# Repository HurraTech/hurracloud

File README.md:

### Dev Environment Setup 

1. Checkout code

        git clone --recurse-submodules https://github.com/hurratech/hurracloud.git
        git submodule foreach --recursive git checkout master
        git submodule foreach --recursive git pull origin master

2. Install dependencies

        # macOS
        brew install go leveldb tmux protoc-gen-go protoc-gen-go-grpc

        # Linux (Fedora)
        dnf install go leveldb leveldb-devel tmux protoc-gen-go

3. Install Air tool (allows hot reload of Golang app)

        curl -sSfL https://raw.githubusercontent.com/cosmtrek/air/master/install.sh | sh -s -- -b /usr/local/bin

3. Install node-modules (only needed first time or when pacakge.json has changed)

        cd src/samaa
        docker run -it -v $(pwd):/app node:14.8.0 bash
        cd /app && npm install
        exit
        cd ../..

4. This will split the terminal windows for you and start all applications (you need to tmux for this, availabla via standard package managers) 

        ./start-all.sh

5. Access the UI at [http://localhost:8080/](http://localhost:8080)

### Option B: Start Components Individually

All Go components can be started manually using Go commands as shown below, or using Air tool, in each go submodule there is a config file `.air.toml` which can be used to run the app as follows:

        air -c .air.toml

The command above should work for all Go submodules. For non-Go submodules (such as Samaa), please see the following subsections.

#### 1. Samaa (UI)

1. Install node-modules

        cd src/samaa
        docker run -it -v $(pwd):/app node:14.8.0 bash
        npm install
        exit

2. Run Docker container

        docker compose up

#### 2. Jawhar (core)
1. Create data directory (one-time)

        cd src/jawhar
        mkdir data # first time

2. Start Application - two options:  

- Using Local Souq service (have to start Souq service - see below)

        go run cmd/jawhar/jawhar.go -S http://127.0.0.1:5060
        # Or simply use air (tool that auto-build and reload whenever Go source code change):
        air -c .air.toml

- Or using Production Souq (https://souq.hurracloud.io - currently down ):

        go run cmd/jawhar/jawhar.go 

#### 3. HAgent (agent)

1. Run application

        cd src/hagent
        sudo go run server.go # sudo is needed for Disk and other privileged operations to work

        # Or simply use air (tool that auto-build and reload whenever Go source code change):
        sudo air -c .air.toml

#### 4. Zahif (files indexer)
*Optional:* Needed for search and indexing functionalities

        cd src/zahif
        go run cmd/zahif/zahif.go

        # Or simply use air (tool that auto-build and reload whenever Go source code change):
        sudo air -c .air.toml

#### 5. Souq (App Store and Update service)
*Optional:* Needed for App Store functionality

        cd src/souq
        go run cmd/souq/souq.go

        # Or simply use air (tool that auto-build and reload whenever Go source code change):
        sudo air -c .air.toml

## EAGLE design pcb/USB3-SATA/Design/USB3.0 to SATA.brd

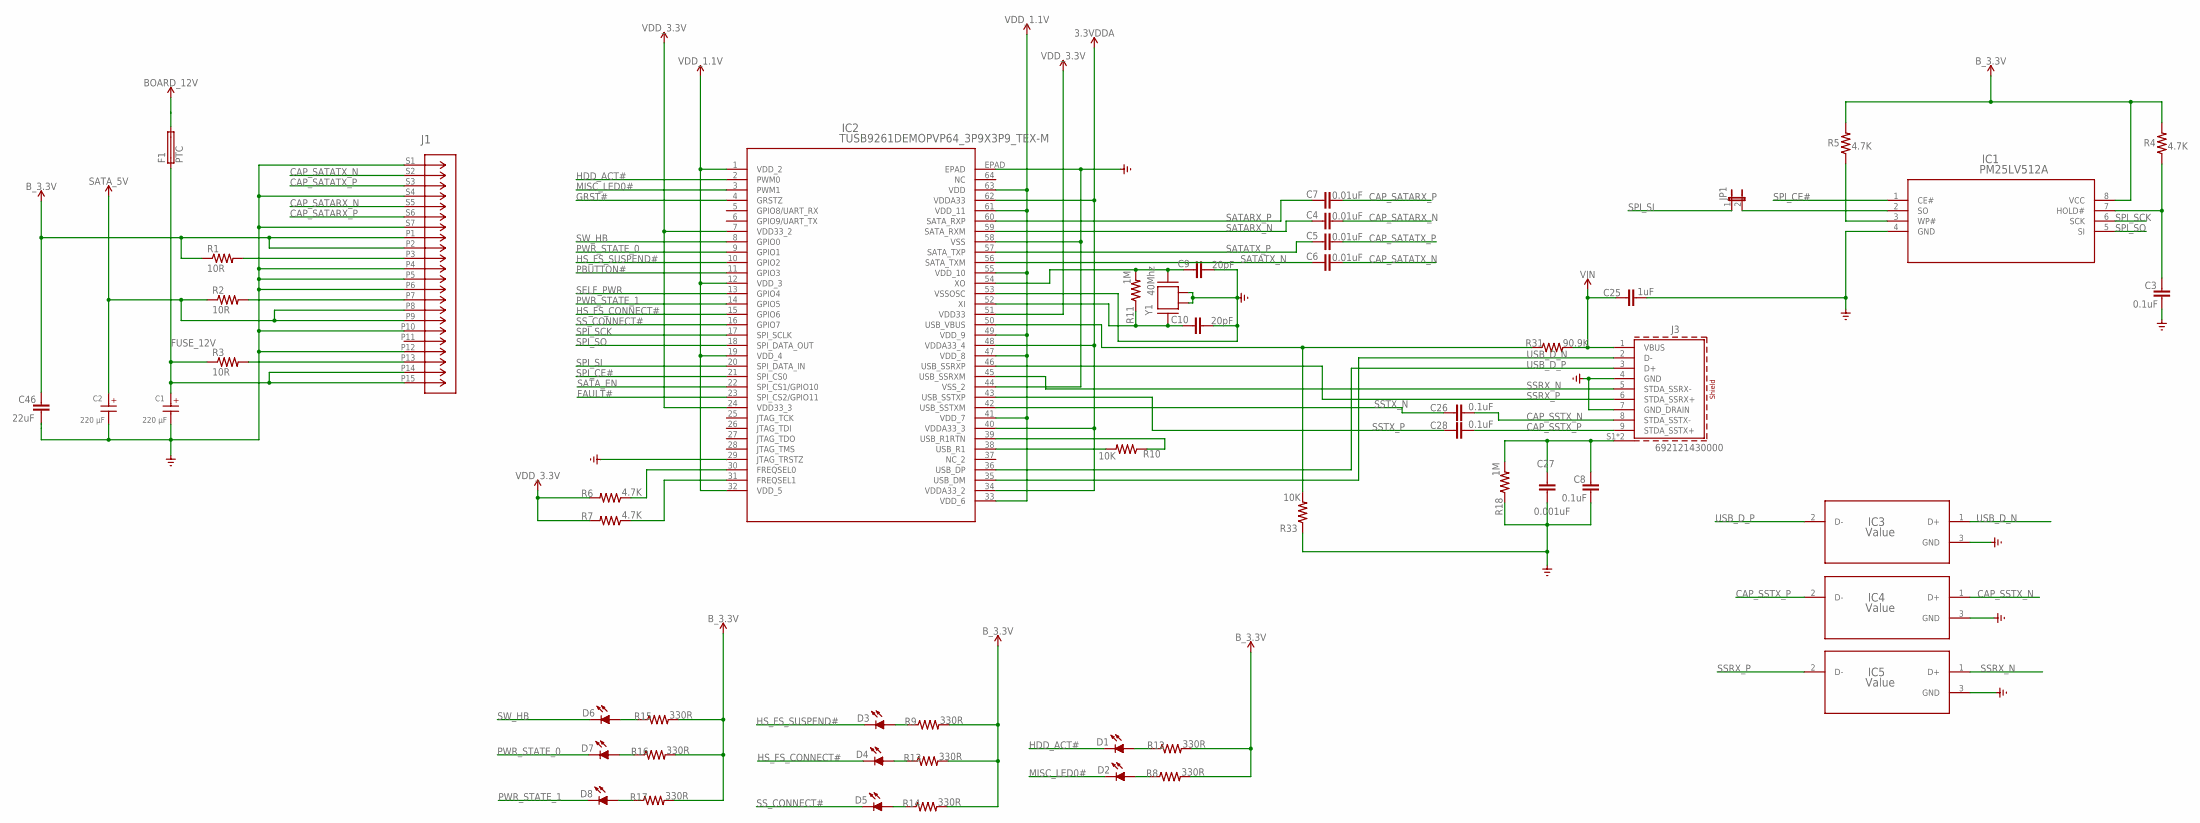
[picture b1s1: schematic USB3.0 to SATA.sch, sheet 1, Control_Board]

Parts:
C1, C2: 220 µF; WCAP-ATUL_8X11.5(DXL); MPN 860040374004
C3, C8, C26, C28: 0.1uF; CAP_0402; MPN CC0402KPX7R7BB104; DIGIKEY_PART_NUMBER 311-3559-1-ND
C4, C5, C6, C7: 0.01uF; CAP_0402; MPN GRM155R71C103KA01J; DIGIKEY_PART_NUMBER 490-6326-1-ND
C9, C10: 20pF; CAP_0402; MPN 04023U200JAT2A; DIGIKEY_PART_NUMBER 478-11758-1-ND
C25: 1uF; CAP_0402; MPN CC0402KRX5R7BB105; DIGIKEY_PART_NUMBER 311-1691-1-ND
C27: 0.001uF; CAP_0402; MPN CC0402KRX7R8BB102; DIGIKEY_PART_NUMBER 311-1712-1-ND
C46: 22uF; CAP_0402; MPN CL05A226MQ5N6J8; DIGIKEY_PART_NUMBER 1276-7090-1-ND
D1, D2, D3, D4, D5, D6, D7, D8: LED_LEDCHIP-LED0603MP; LED_CHIP-LED0603MP; DIGIKEY_PART_NUMBER 2460-L196L-SGC-TR-ND
F1: PTC; FUSC3215X82N; MPN 400CC1206LR-C-2
IC1: PM25LV512A; SOIC8-N_MC_MCH
IC2: TUSB9261DEMOPVP64_3P9X3P9_TEX-M; PVP64_3P9X3P9_TEX-M
IC3, IC4, IC5: Value; DRT0003A
J1: 10031569-001LF; CONN_10031569-001LF_AMP
J3: 692121430000
JP1: JP1E; JP1
R1, R2, R3: 10R; RES_0603; MPN SDR03EZPF10R0; DIGIKEY_PART_NUMBER 511-1693-1-ND
R4, R5, R6, R7: 4.7K; RES_0402; MPN RT0402BRD074K7L; DIGIKEY_PART_NUMBER YAG1446CT-ND
R8, R9, R12, R13, R14, R15, R16, R17: 330R; RES_0603; MPN SDR03EZPJ331; DIGIKEY_PART_NUMBER 511-1764-1-ND
R10, R33: 10K; RES_0402; MPN RCG04021M00FKED; DIGIKEY_PART_NUMBER 541-1752-1-ND
R11, R18: 1M; RES_0402; MPN RE0402BRE071ML; DIGIKEY_PART_NUMBER 13-RE0402BRE071MLCT-ND
R31: 90.9K; RES_0402; MPN RT0402DRE0790K9L; DIGIKEY_PART_NUMBER 311-2334-1-ND
Y1: 40Mhz; ABM3B-40.000MHZ-B2-T

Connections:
2.8V: IC2.7 (VDD33_2), IC2.24 (VDD33_3), IC2.51 (VDD33), R6.2, R7.2; also elsewhere on the board
3.3VDDA: IC2.34 (VDDA33_2), IC2.40 (VDDA33_3), IC2.48 (VDDA33_4), IC2.62 (VDDA33); also elsewhere on the board
5V: C2.1 (+), J1.P8, J1.P9, R2.1; also elsewhere on the board
12V: F1.2; also elsewhere on the board
B_3.3V: C46.2, IC1.8 (VCC), J1.P1, J1.P2, R1.1, R4.2, R5.2, R8.2, R9.2, R12.2, R13.2, R14.2, R15.2, R16.2, R17.2; also elsewhere on the board
CAP_SATARX_N: C4.2, J1.S5
CAP_SATARX_P: C7.2, J1.S6
CAP_SATATX_N: C6.2, J1.S2
CAP_SATATX_P: C5.2, J1.S3
CAP_SSTX_N: C26.1, IC4.1 (D+), J3.8 (STDA_SSTX-)
CAP_SSTX_P: C28.1, IC4.2 (D-), J3.9 (STDA_SSTX+)
FAULT#: IC2.23 (SPI_CS2/GPIO11); also elsewhere on the board
FUSE_12V: C1.1 (+), F1.1, J1.P14, J1.P15, R3.1
GND: C1.2 (-), C2.2 (-), C3.1, C8.1, C9.2, C10.2, C25.1, C27.2, C46.1, IC1.4 (GND), IC2.29 (JTAG_TRSTZ), IC2.44 (VSS_2), IC2.53 (VSSOSC), IC2.58 (VSS), IC2.EPAD, IC3.3 (GND), IC4.3 (GND), IC5.3 (GND), J1.P4, J1.P5, J1.P6, J1.P10, J1.P12, J1.S1, J1.S4, J1.S7, J3.4 (GND), J3.7 (GND_DRAIN), R18.1, R33.1, Y1.2, Y1.4; also elsewhere on the board
GRST#: IC2.4 (GRSTZ); also elsewhere on the board
HDD_ACT#: D1.C, IC2.2 (PWM0)
HS_FS_CONNECT#: D4.C, IC2.15 (GPIO6)
HS_FS_SUSPEND#: D3.C, IC2.10 (GPIO2)
MISC_LED0#: D2.C, IC2.3 (PWM1)
unnamed: J1.P3, R1.2
unnamed: J1.P13, R3.2
unnamed: J1.P7, R2.2
unnamed: IC1.2 (SO), JP1.2
unnamed: IC1.3 (WP#), R5.1
unnamed: C3.2, IC1.7 (HOLD#), R4.1
unnamed: IC2.30 (FREQSEL0), R6.1
unnamed: IC2.31 (FREQSEL1), R7.1
unnamed: IC2.38 (USB_R1), R10.2
unnamed: IC2.39 (USB_R1RTN), R10.1
unnamed: C10.1, IC2.52 (XI), R11.1, Y1.1
unnamed: C9.1, IC2.54 (XO), R11.2, Y1.3
unnamed: D1.A, R12.1
unnamed: D2.A, R8.1
unnamed: D3.A, R9.1
unnamed: D4.A, R13.1
unnamed: D5.A, R14.1
unnamed: D6.A, R15.1
unnamed: D7.A, R16.1
unnamed: D8.A, R17.1
unnamed: IC2.50 (USB_VBUS), R31.1, R33.2
unnamed: C8.2, C27.1, J3.S1 (SHIELD), J3.S2 (SHIELD), R18.2
PBUTTON#: IC2.11 (GPIO3)
PWR_STATE_0: D7.C, IC2.9 (GPIO1)
PWR_STATE_1: D8.C, IC2.14 (GPIO5)
SATARX_N: C4.1, IC2.59 (SATA_RXM)
SATARX_P: C7.1, IC2.60 (SATA_RXP)
SATATX_N: C6.1, IC2.56 (SATA_TXM)
SATATX_P: C5.1, IC2.57 (SATA_TXP)
SATA_EN: IC2.22 (SPI_CS1/GPIO10); also elsewhere on the board
SELF_PWR: IC2.13 (GPIO4)
SPI_CE#: IC1.1 (CE#), IC2.21 (SPI_CS0)
SPI_SCK: IC1.6 (SCK), IC2.17 (SPI_SCLK)
SPI_SI: IC2.20 (SPI_DATA_IN), JP1.1
SPI_SO: IC1.5 (SI), IC2.18 (SPI_DATA_OUT)
SSRX_N: IC2.45 (USB_SSRXM), IC5.1 (D+), J3.5 (STDA_SSRX-)
SSRX_P: IC2.46 (USB_SSRXP), IC5.2 (D-), J3.6 (STDA_SSRX+)
SSTX_N: C26.2, IC2.42 (USB_SSTXM)
SSTX_P: C28.2, IC2.43 (USB_SSTXP)
SS_CONNECT#: D5.C, IC2.16 (GPIO7)
SW_HB: D6.C, IC2.8 (GPIO0)
USB_D_N: IC2.35 (USB_DM), IC3.1 (D+), J3.2 (D-)
USB_D_P: IC2.36 (USB_DP), IC3.2 (D-), J3.3 (D+)
VDD_1.1V: IC2.1 (VDD_2), IC2.12 (VDD_3), IC2.19 (VDD_4), IC2.32 (VDD_5), IC2.33 (VDD_6), IC2.41 (VDD_7), IC2.47 (VDD_8), IC2.49 (VDD_9), IC2.55 (VDD_10), IC2.61 (VDD_11), IC2.63 (VDD); also elsewhere on the board
VIN: C25.2, J3.1 (VBUS), R31.2; also elsewhere on the board

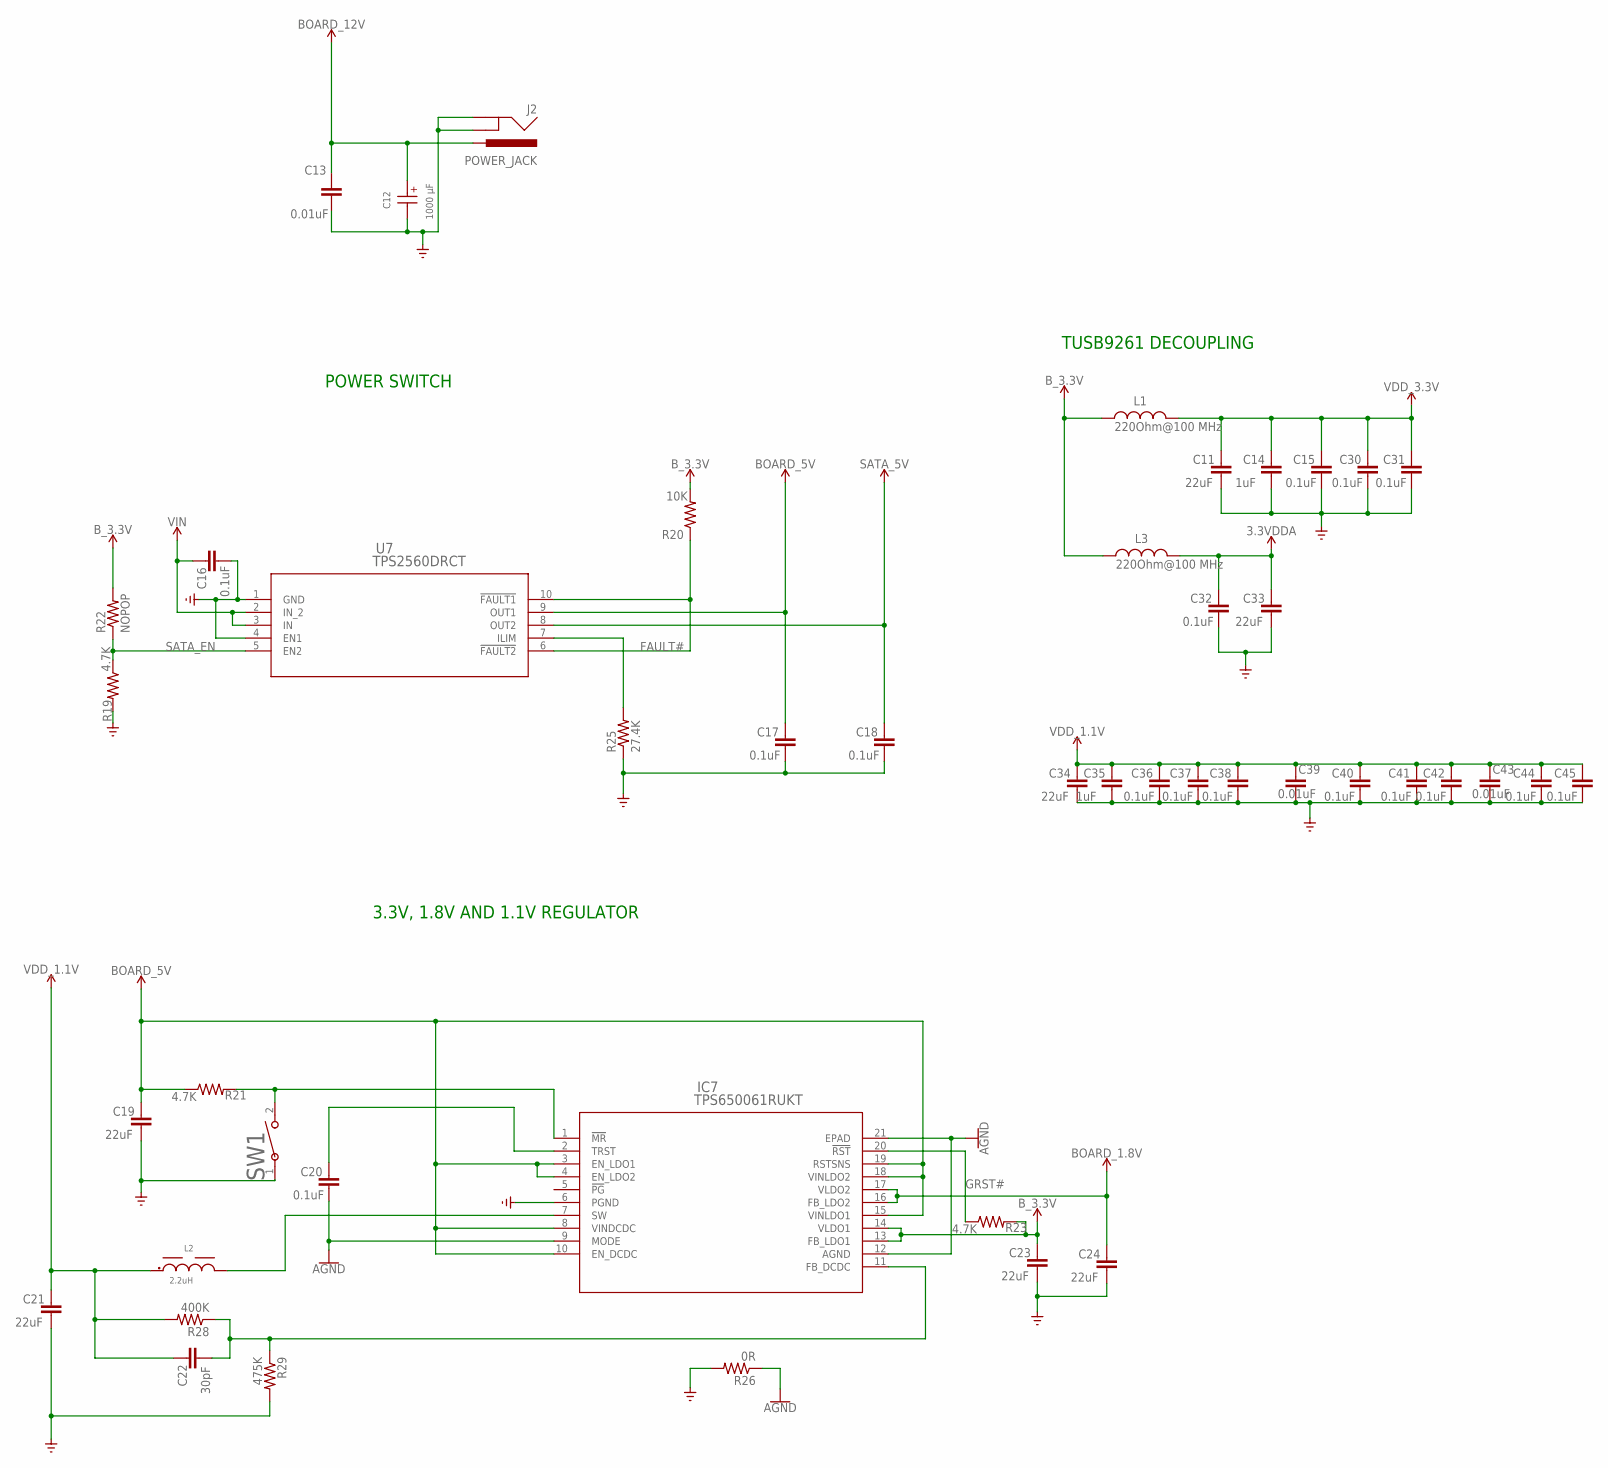
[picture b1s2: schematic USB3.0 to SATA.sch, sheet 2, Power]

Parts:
C11, C19, C21, C23, C24, C33, C34: 22uF; CAP_0402; MPN CL05A226MQ5N6J8; DIGIKEY_PART_NUMBER 1276-7090-1-ND
C12: 1000 µF; WCAP-ATLL_10X16(DXL); MPN 860160375032
C13, C39, C43: 0.01uF; CAP_0402; MPN GRM155R71C103KA01J; DIGIKEY_PART_NUMBER 490-6326-1-ND
C14, C35: 1uF; CAP_0402; MPN CC0402KRX5R7BB105; DIGIKEY_PART_NUMBER 311-1691-1-ND
C15, C16, C17, C18, C20, C30, C31, C32, C36, C37, C38, C40, C41, C42, C44, C45: 0.1uF; CAP_0402; MPN CC0402KPX7R7BB104; DIGIKEY_PART_NUMBER 311-3559-1-ND
C22: 30pF; CAP_0402; MPN GRM1555C1E300JA01D; DIGIKEY_PART_NUMBER 490-7752-1-ND
IC7: TPS650061RUKT; RUK20_1P7X1P7
J2: POWER_JACK; POWER_JACK_PTH
L1, L3: 220Ohm@100 MHz; WE-CBF_0603(W=2.2); MPN 74279263
L2: 2.2uH; WE-MAPI_4020
R19, R21, R23: 4.7K; RES_0402; MPN RT0402BRD074K7L; DIGIKEY_PART_NUMBER YAG1446CT-ND
R20: 10K; RES_0402; MPN RCG04021M00FKED; DIGIKEY_PART_NUMBER 541-1752-1-ND
R22: NOPOP; RES_0402
R25: 27.4K; RES_0402; MPN RT0402DRD0727K4L; DIGIKEY_PART_NUMBER YAG4427CT-ND
R26: 0R; RES_0402; MPN AC0402FR-070RL; DIGIKEY_PART_NUMBER 13-AC0402FR-070RLCT-ND
R28: 400K; RES_0402; MPN CR204003F; DIGIKEY_PART_NUMBER 2997-CR204003FTR-ND
R29: 475K; RES_0402; MPN RC0402FR-07475KL; DIGIKEY_PART_NUMBER 311-475KLRCT-ND
SW1: EVP-AWED2A; SW_EVP-AWED2A_PAN
U7: TPS2560DRCT; DRC10_2P4X1P65

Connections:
1.8V: C24.2, IC7.16 (FB_LDO2), IC7.17 (VLDO2)
2.8V: C11.2, C14.2, C15.2, C30.2, C31.2, L1.2; also elsewhere on the board
3.3VDDA: C32.2, C33.2, L3.2; also elsewhere on the board
5V: C18.2, U7.8 (OUT2); also elsewhere on the board
12V: C12.1 (+), C13.1, J2.PWR; also elsewhere on the board
AGND: C20.1, IC7.9 (MODE), IC7.12 (AGND), IC7.21 (EPAD), R26.1
BOARD_5V: C17.2, C19.2, IC7.3 (EN_LDO1), IC7.4 (EN_LDO2), IC7.8 (VINDCDC), IC7.10 (EN_DCDC), IC7.15 (VINLDO1), IC7.18 (VINLDO2), IC7.19 (RSTSNS), R21.1, U7.9 (OUT1)
B_3.3V: C23.2, IC7.13 (FB_LDO1), IC7.14 (VLDO1), L1.1, L3.1, R20.2, R22.2, R23.2; also elsewhere on the board
FAULT#: R20.1, U7.6 (!FAULT2), U7.10 (!FAULT1); also elsewhere on the board
GND: C11.1, C12.2 (-), C13.2, C14.1, C15.1, C16.1, C17.1, C18.1, C19.1, C21.1, C23.1, C24.1, C30.1, C31.1, C32.1, C33.1, C34.1, C35.1, C36.1, C37.1, C38.1, C39.2, C40.1, C41.1, C42.1, C43.2, C44.1, C45.1, IC7.6 (PGND), J2.GND, J2.GNDBREAK, R19.2, R25.1, R26.2, R29.2, SW1.1, U7.1 (GND), U7.4 (EN1); also elsewhere on the board
GRST#: IC7.20 (!RST), R23.1; also elsewhere on the board
unnamed: IC7.1 (!MR), R21.2, SW1.2
unnamed: R25.2, U7.7 (ILIM)
unnamed: C20.2, IC7.2 (TRST)
unnamed: IC7.7 (SW), L2.2
unnamed: C22.1, IC7.11 (FB_DCDC), R28.1, R29.1
SATA_EN: R19.1, R22.1, U7.5 (EN2); also elsewhere on the board
VDD_1.1V: C21.2, C22.2, C34.2, C35.2, C36.2, C37.2, C38.2, C39.1, C40.2, C41.2, C42.2, C43.1, C44.2, C45.2, L2.1, R28.2; also elsewhere on the board
VIN: C16.2, U7.2 (IN_2), U7.3 (IN); also elsewhere on the board

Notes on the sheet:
POWER SWITCH
3.3V, 1.8V AND 1.1V REGULATOR
TUSB9261 DECOUPLING

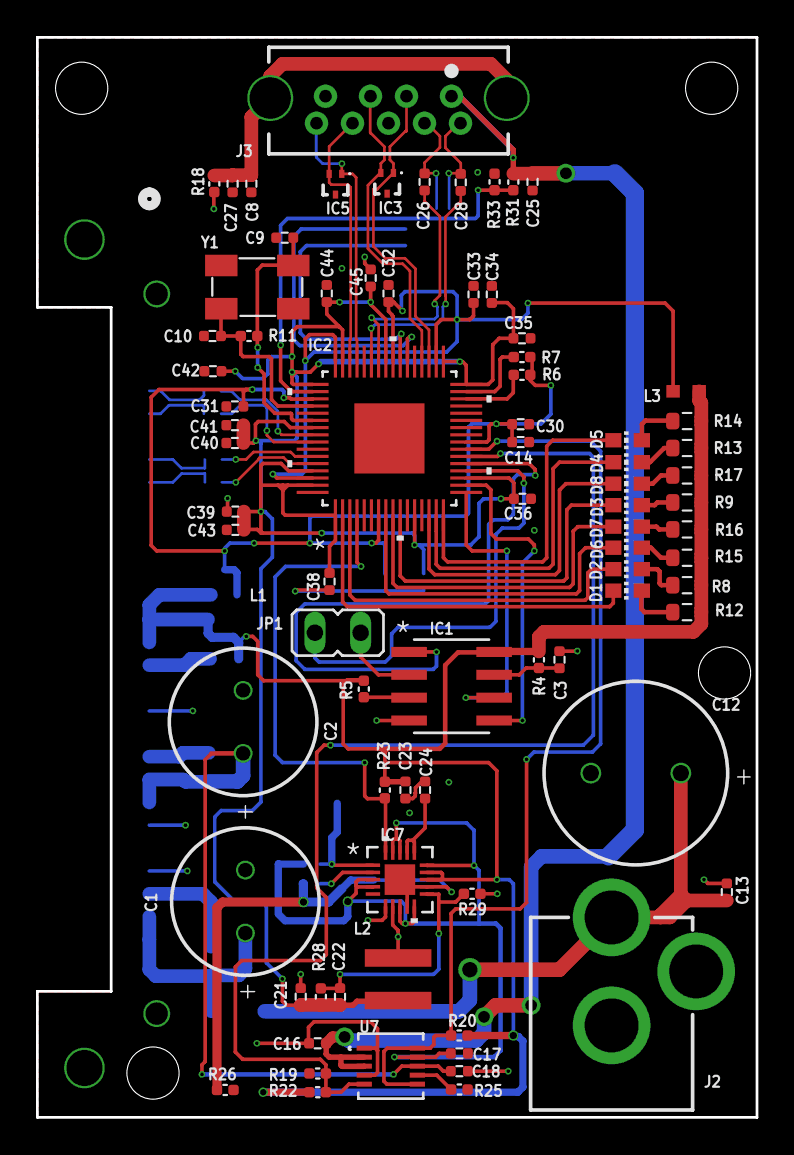
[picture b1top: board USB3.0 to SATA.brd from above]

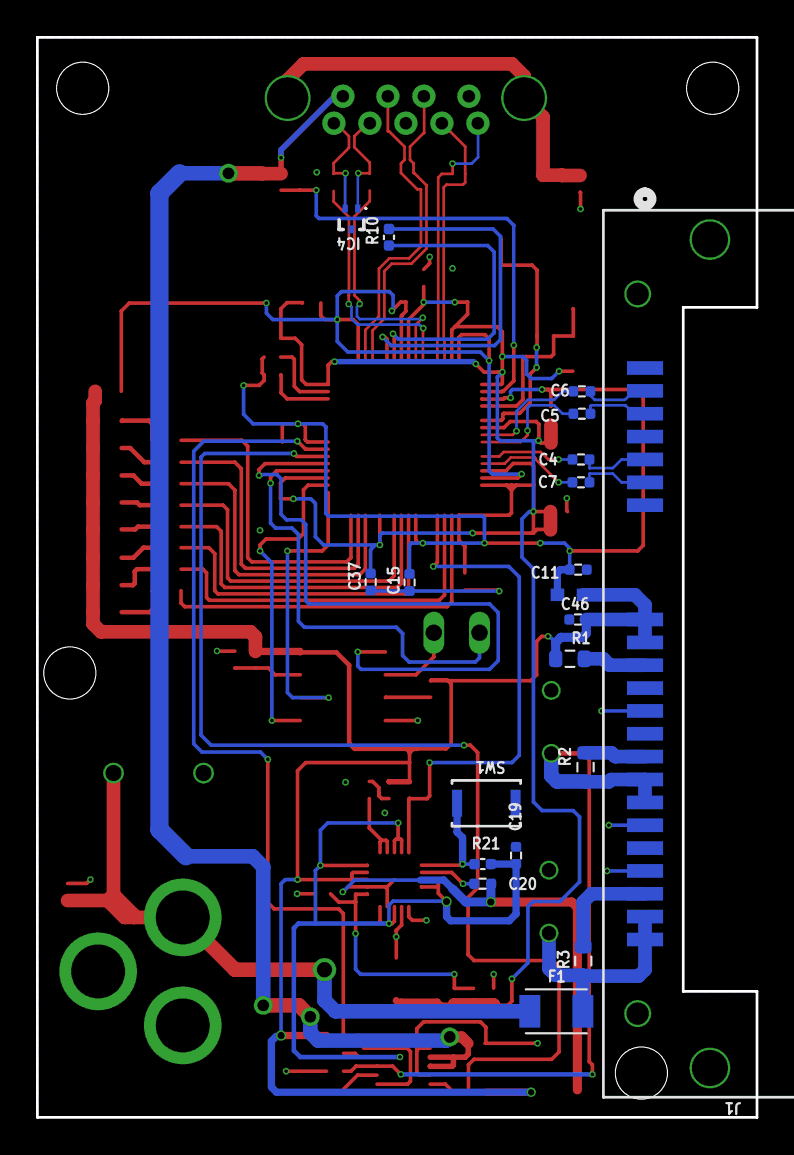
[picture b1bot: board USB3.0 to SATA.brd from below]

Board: 2 copper layers, 40.0 x 60.0 mm, 99 parts (20 on the bottom side), 70 nets.

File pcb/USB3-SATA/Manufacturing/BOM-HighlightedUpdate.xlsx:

Qty | Designator | Value | DNI | PACKAGE | Footprint | Manufacturer Product Number | Distributor Part Number (DigiKey) | Comment | LCLS Part # | Description
1 | JP1 |  |  | TH | 5.08x2.8 | 75160-101-02LF | 609-75160-101-02LF-ND | CONN HEADER VERT 2POS 2.54MM | C239401 | Connector Header Through Hole 2 position 0.100" (2.54mm)
8 | D1, D2, D3, D4, D5, D6, D7, D8 |  |  | SMT | 1608 | SML-D12M1WT86 | SML-D12M1WT86CT-ND | LED YLW/GREEN DIFFUSED 1608 SMD | C72042 | Yellow-Green 572nm LED Indication - Discrete 2.2V 0603 (1608 Metric)
1 | C27 | 0.001uF |  | SMT | 402 | CC0402KRX7R8BB102 | 311-1712-1-ND | CAP CER 1000PF 25V X7R 0402 | C188845 | 1000pF ±10% 25V Ceramic Capacitor X7R 0402 (1005 Metric)
7 | C4, C5, C6, C7, C13, C39, C43 | 0.01uF |  | SMT | 402 | GRM155R71C103KA01J | 490-6326-1-ND | CAP CER 10000PF 16V X7R 0402 | C15195 | 10000pF ±10% 16V Ceramic Capacitor X7R 0402 (1005 Metric)
20 | C3, C8, C15, C16, C17, C18, C20, C26, C28, C30, C31, C32, C36, C37, C38, C40, C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 | 0.1uF |  | SMT | 402 | CC0402KPX7R7BB104 | 311-3559-1-ND | CAP CER 0.1UF 16V X7R 0402 | C361198 | 0.1µF ±10% 16V Ceramic Capacitor X7R 0402 (1005 Metric)
1 | R26 | 0R |  | SMT | 402 | RC0402JR-070RL | 311-0.0JRCT-ND | RESISTOR 0402 JUMPER ZERO OHM | C17168 | 0 Ohms Jumper 0.063W, 1/16W Chip Resistor 0402 (1005 Metric) Automotive AEC-Q20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
1 | C12 | 1000 µF |  | TH | Radial, 10x17.5 | 860160375032 | 860160375032 | CAP 1000 UF 20% 16 V | C43828 | 1000µF 16V Aluminum Electrolytic Capacitors Radial, Can 6000 Hrs @ 105°C
1 | J1 |  |  | SMT | 42.5x5.5 | 10034814-001LF | 609-1035-ND | CONN SATA RCPT 22POS SLD R/A SMD |  | 22 Position SATA Receptacle Connector Solder Surface Mount, Right Angle
3 | R10, R20, R33 | 10K |  | SMT | 402 | RNCF0402BTE10K0 | RNCF0402BTE10K0CT-ND | RES 10K OHM 0.1% 1/16W 0402 | C84351 | 10 kOhms ±0.1% 0.063W, 1/16W Chip Resistor 0402 (1005 Metric) Automotive AEC-Q2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
3 | R1, R2, R3 | 10 |  | SMT | 603 | SDR03EZPF10R0 | 511-1693-1-ND | RES SMD 10 OHM 1% 0.3W 0603 |  | 10 Ohms ±1% 0.3W Chip Resistor 0603 (1608 Metric) Pulse Withstanding Thick Film
2 | R11, R18 | 1M |  | SMT | 402 | RCG04021M00FKED | 541-1752-1-ND | RES SMD 1M OHM 1% 1/16W 0402 | C185077 | 1 MOhms ±1% 0.063W, 1/16W Chip Resistor 0402 (1005 Metric) Thick Film
3 | C14, C25, C35 | 1uF |  | SMT | 402 | CC0402KRX5R7BB105 | 311-1691-1-ND | CAP CER 1UF 16V X5R 0402 | C29266 | 1µF ±10% 16V Ceramic Capacitor X5R 0402 (1005 Metric)
1 | L2 | 2.2uH |  | SMT | SMD-2 | 74438356022 | 732-8232-2-ND | FIXED IND 2.2UH 4.7A 35 MOHM SMD |  | 2.2µH Shielded Molded Inductor 4.7A 35mOhm Max 2-SMD
2 | C9, C10 | 20pF |  | SMT | 402 | 04023U200JAT2A | 478-11758-1-ND | CAP CER 20PF 25V NP0 0402 | C1554 | 20pF ±5% 25V Ceramic Capacitor C0G, NP0 0402 (1005 Metric)
2 | C1, C2 | 220 µF |  | TH | Radial, 8x13 | 860040374004 | 732-9153-1-ND | CAP 220 UF 20% 16 V | C43349 | 220µF 16V Aluminum Electrolytic Capacitors Radial, Can 7000 Hrs @ 105°C
2 | L1, L3 | 220Ohm@100 MHz |  | SMT | 603 | 74279263 | 732-1581-1-ND | FERRITE BEAD 220 OHM 0603 1LN |  | 220 Ohms @ 100MHz 1 Signal Line Ferrite Bead 0603 (1608 Metric) 500mA 300mOhm
8 | C11, C19, C21, C23, C24, C33, C34, C46 | 22uF |  | SMT | 402 | CL05A226MQ5N6J8 | 1276-7090-1-ND | CAP CER 22UF 6.3V X5R 0402 | C59461 | 22µF ±20% 6.3V Ceramic Capacitor X5R 0402 (1005 Metric)
1 | R25 | 27.4K |  | SMT | 402 | RT0402DRD0727K4L | YAG4427CT-ND | RES SMD 27.4KOHM 0.5% 1/16W 0402 | C26971 | 27.4 kOhms ±0.5% 0.063W, 1/16W Chip Resistor 0402 (1005 Metric) Thin Film
1 | C22 | 30pF |  | SMT | 402 | GRM1555C1E300JA01D | 490-7752-1-ND | CAP CER 30PF 25V C0G/NP0 0402 | C1570 | 30pF ±5% 25V Ceramic Capacitor C0G, NP0 0402 (1005 Metric)
8 | R8, R9, R12, R13, R14, R15, R16, R17 | 330R |  | SMT | 603 | SDR03EZPJ331 | 511-1764-1-ND | RES SMD 330 OHM 5% 0.3W 0603 | C23138 | 330 Ohms ±5% 0.3W Chip Resistor 0603 (1608 Metric) Pulse Withstanding Thick Film
7 | R4, R5, R6, R7, R19, R21, R23 | 4.7K |  | SMT | 402 | RT0402BRD074K7L | YAG1446CT-ND | RES SMD 4.7K OHM 0.1% 1/16W 0402 | C25900 | 4.7 kOhms ±0.1% 0.063W, 1/16W Chip Resistor 0402 (1005 Metric) Thin Film
1 | R28 | 400K |  | SMT | 402 | RCS0402390KFKED | 541-RCS0402390KFKEDCT-ND | RES SMD 390K OHM 1% 1/5W 0402 | C25785 | 390 kOhms ±1% 0.2W, 1/5W Chip Resistor 0402 (1005 Metric) Automotive AEC-Q200, 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
1 | Y1 | 40Mhz |  | SMT | 5.0x3.2 | ABM3C-40.000MHZ-D4Y-T | 535-11304-2-ND | CRYSTAL 40.0000MHZ 18PF SMD | C295515 | 40MHz ±30ppm Crystal 18pF 50 Ohms 4-SMD, No Lead
1 | R29 | 475K |  | SMT | 402 | RC0402FR-07475KL | 311-475KLRCT-ND | RES SMD 475K OHM 1% 1/16W 0402 | C25791 | 475 kOhms ±1% 0.063W, 1/16W Chip Resistor 0402 (1005 Metric) Moisture Resistant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
1 | J3 |  |  | TH | 15.6x6.9 | 692121430000 | 732-5253-ND | CONN RCPT USB3.0 TYPEA 9POS VERT | C388645 | USB-A (USB TYPE-A) USB 3.2 Gen 1 (USB 3.1 Gen 1, Superspeed (USB 3.0)) Receptac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
1 | R31 | 90.9K |  | SMT | 402 | RT0402DRE0790K9L | 311-2334-1-ND | RES SMD 90.9KOHM 0.5% 1/16W 0402 | C26989 | 90.9 kOhms ±0.5% 0.063W, 1/16W Chip Resistor 0402 (1005 Metric) Thin Film
1 | SW1 | EVP-AWED2A |  | SMT | 3x2 | EVP-AWED2A | P19745CT-ND | SWITCH TACTILE SPST-NO 0.02A 15V | C140848 | Tactile Switch SPST-NO Top Actuated Surface Mount
1 | R22 | NOPOP | Y | SMT |  |  |  | DO NOT POPULATE |  | Do not install
1 | IC1 | PM25LV512A |  | SMT | 8-SOIC, 3.9x4.8 | AT25DN512C-SSHF-B | 1265-1183-5-ND | IC FLASH 512KBIT SPI 8SOIC | C401657 | FLASH Memory IC 512Kb (64K x 8) SPI 104MHz 8-SOIC
1 | J2 | POWER_JACK |  | TH | 14.4x9 | PJ-202AH | CP-202AH-ND | CONN PWR JACK 2X5.5MM KINKED PIN | C16214 | Power Barrel Connector Jack 2.10mm ID (0.083"), 5.50mm OD (0.217") Through Hole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
1 | F1 | PTC |  | SMT | 1206 | 0ZCJ0075AF2E | 507-1805-2-ND | PTC RESET FUSE 16V 750MA 1206 | C70080 | Polymeric PTC Resettable Fuse 16V 750mA Ih Surface Mount 1206 (3216 Metric), Co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
1 | U7 | TPS2560DRCT |  | QFN | 3x3 | TPS2561DRCT | 296-25548-2-ND | IC PWR SWITCH N-CHAN 1:2 10VSON |  | Power Switch/Driver 1:2 N-Channel 2.5A 10-VSON (3x3)
1 | IC7 | TPS650061RUKT |  | QFN | 1212 | TPS650061RUKT | 296-25358-2-ND | IC CONV STPDWN 2.25MHZ DL 20WQFN |  | IC CONV STPDWN 2.25MHZ DL 20WQFN
1 | IC2 | TUSB9261PVP |  | QFN | 7x7 | TUSB9261PVP | 296-28827-ND | IC INTFACE SPECIALIZED 64HTQFP |  | HDD, CD, DVD Drive Interface 64-HTQFP (7x7)
3 | IC3, IC4, IC5 |  |  | SMT | 1x0.8 | TPD2EUSB30DRTR | 296-25509-1-ND | TVS DIODE 5.5V 8V SOT3 |  | 8V Clamp 1A (8/20µs) Ipp Tvs Diode Surface Mount SOT-9x3

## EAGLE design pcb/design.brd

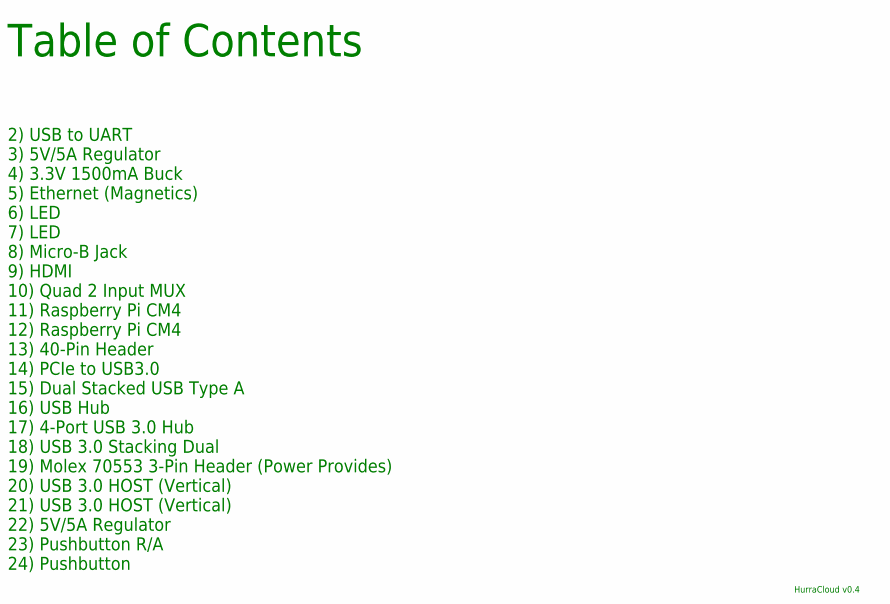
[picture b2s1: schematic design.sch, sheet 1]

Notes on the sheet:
Table of Contents
HurraCloud v0.4
2) USB to UART
3) 5V/5A Regulator
4) 3.3V 1500mA Buck
5) Ethernet (Magnetics)
6) LED
7) LED
8) Micro-B Jack
9) HDMI
10) Quad 2 Input MUX
11) Raspberry Pi CM4
12) Raspberry Pi CM4
13) 40-Pin Header
14) PCIe to USB3.0
15) Dual Stacked USB Type A
16) USB Hub
17) 4-Port USB 3.0 Hub
18) USB 3.0 Stacking Dual
19) Molex 70553 3-Pin Header (Power Provides)
20) USB 3.0 HOST (Vertical)
21) USB 3.0 HOST (Vertical)
22) 5V/5A Regulator
23) Pushbutton R/A
24) Pushbutton

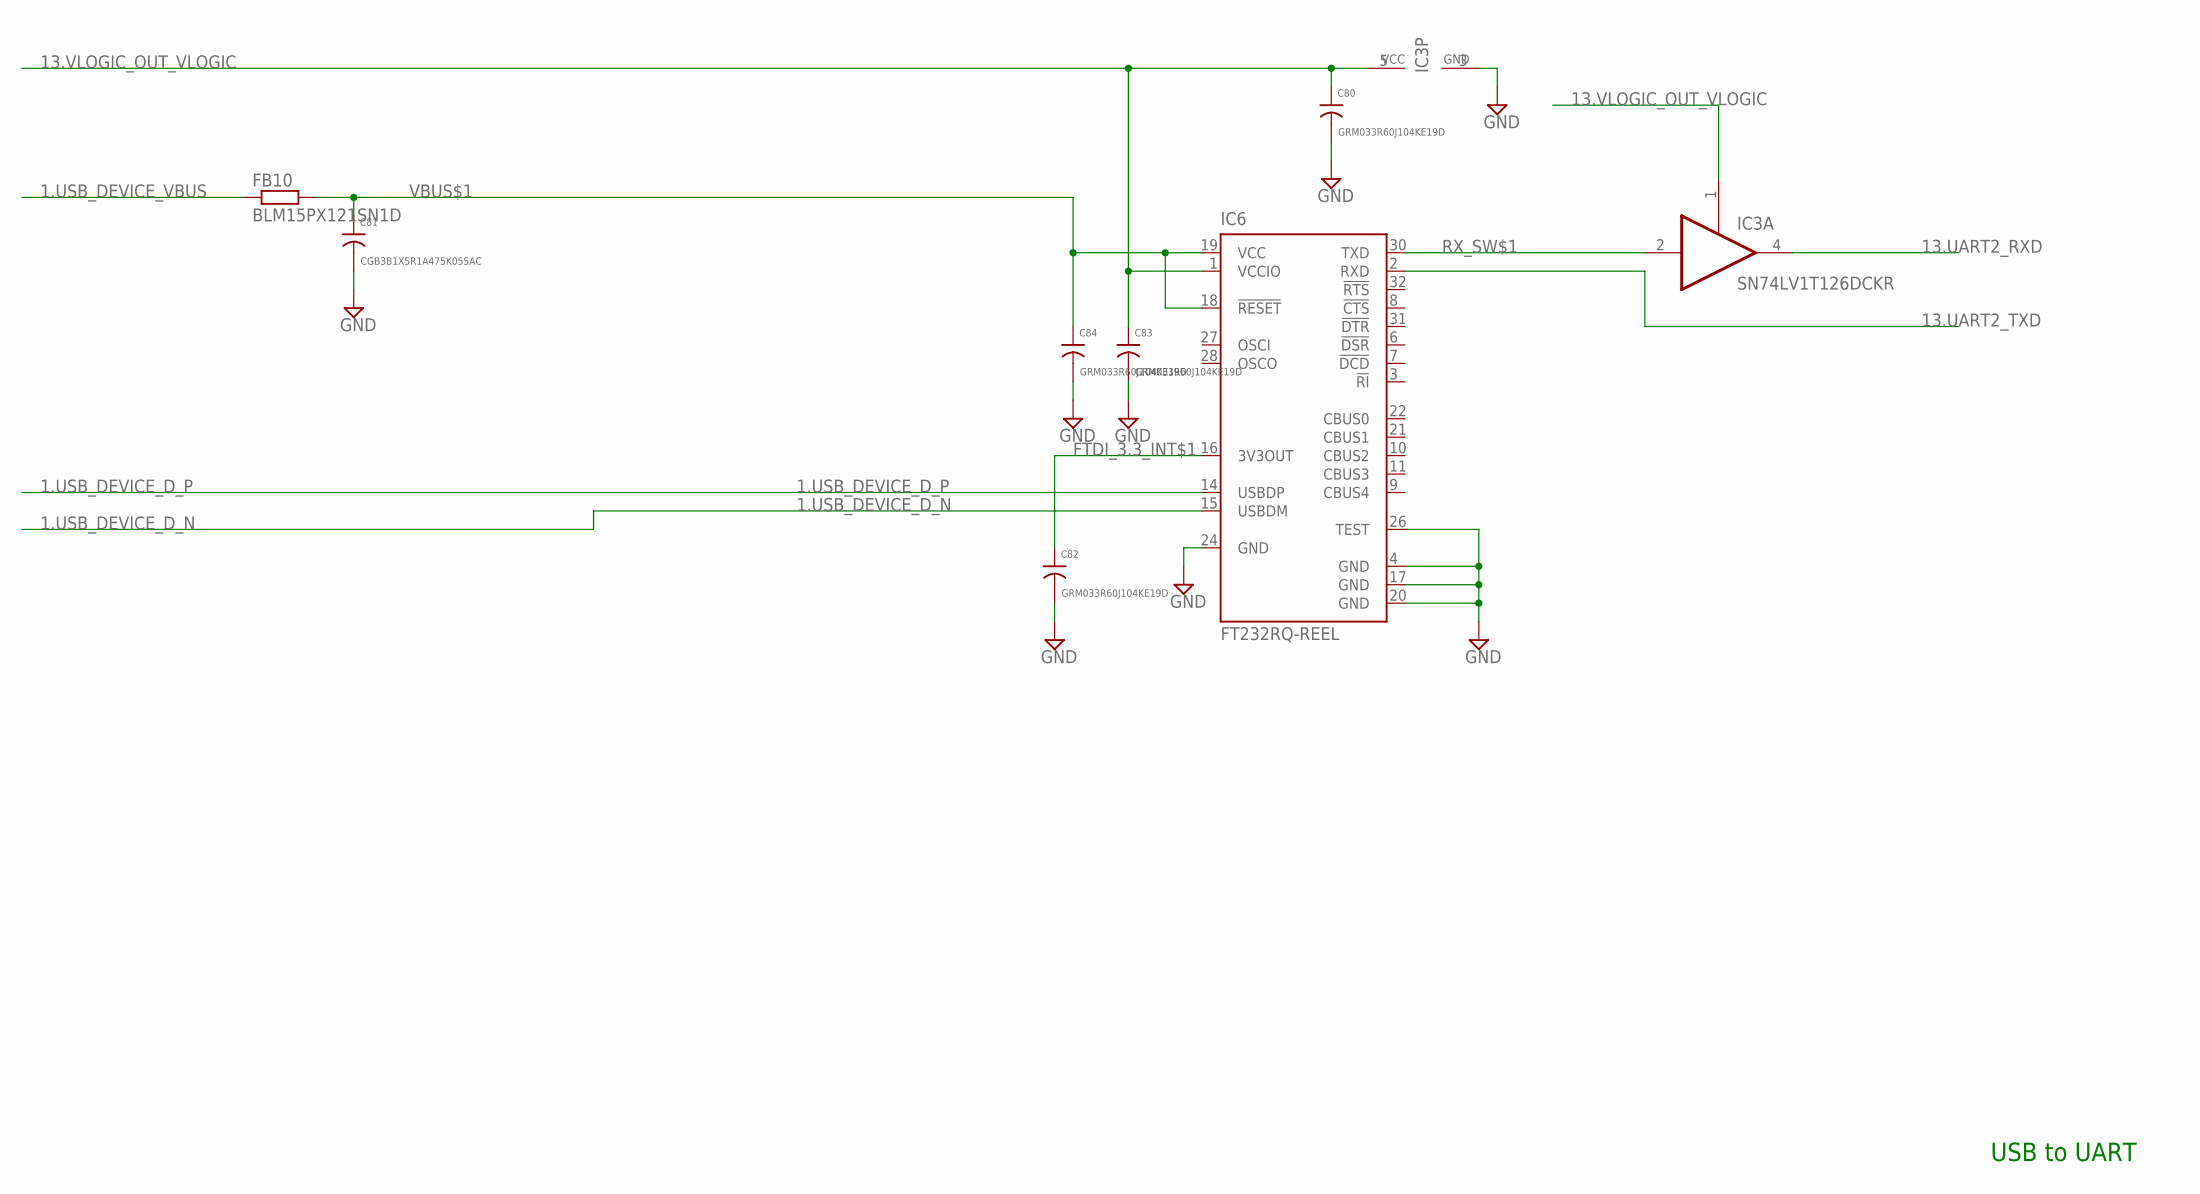
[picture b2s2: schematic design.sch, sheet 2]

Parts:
C80, C82, C83, C84: GRM033R60J104KE19D; 0201
C81: CGB3B1X5R1A475K055AC; 0603
FB10: BLM15PX121SN1D; 0402
IC3: SN74LV1T126DCKR; SC70-5
IC6: FT232RQ-REEL; QFN32

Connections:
1.USB_DEVICE_D_N: IC6.15 (USBDM); also elsewhere on the board
1.USB_DEVICE_D_P: IC6.14 (USBDP); also elsewhere on the board
1.USB_DEVICE_VBUS: FB10.1; also elsewhere on the board
13.UART2_RXD: IC3.4 (O); also elsewhere on the board
13.UART2_TXD: IC6.2 (RXD); also elsewhere on the board
13.VLOGIC_OUT_VLOGIC: C80.1, C83.1, IC3.1 (OE), IC3.5 (VCC), IC6.1 (VCCIO); also elsewhere on the board
FTDI_3.3_INT$1: C82.1, IC6.16 (3V3OUT)
GND: C80.2, C81.2, C82.2, C83.2, C84.2, IC3.3 (GND), IC6.4 (GND), IC6.17 (GND), IC6.20 (GND), IC6.24 (GND), IC6.26 (TEST); also elsewhere on the board
RX_SW$1: IC3.2 (I), IC6.30 (TXD)
VBUS$1: C81.1, C84.1, FB10.2, IC6.18 (!RESET), IC6.19 (VCC)

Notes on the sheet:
USB to UART

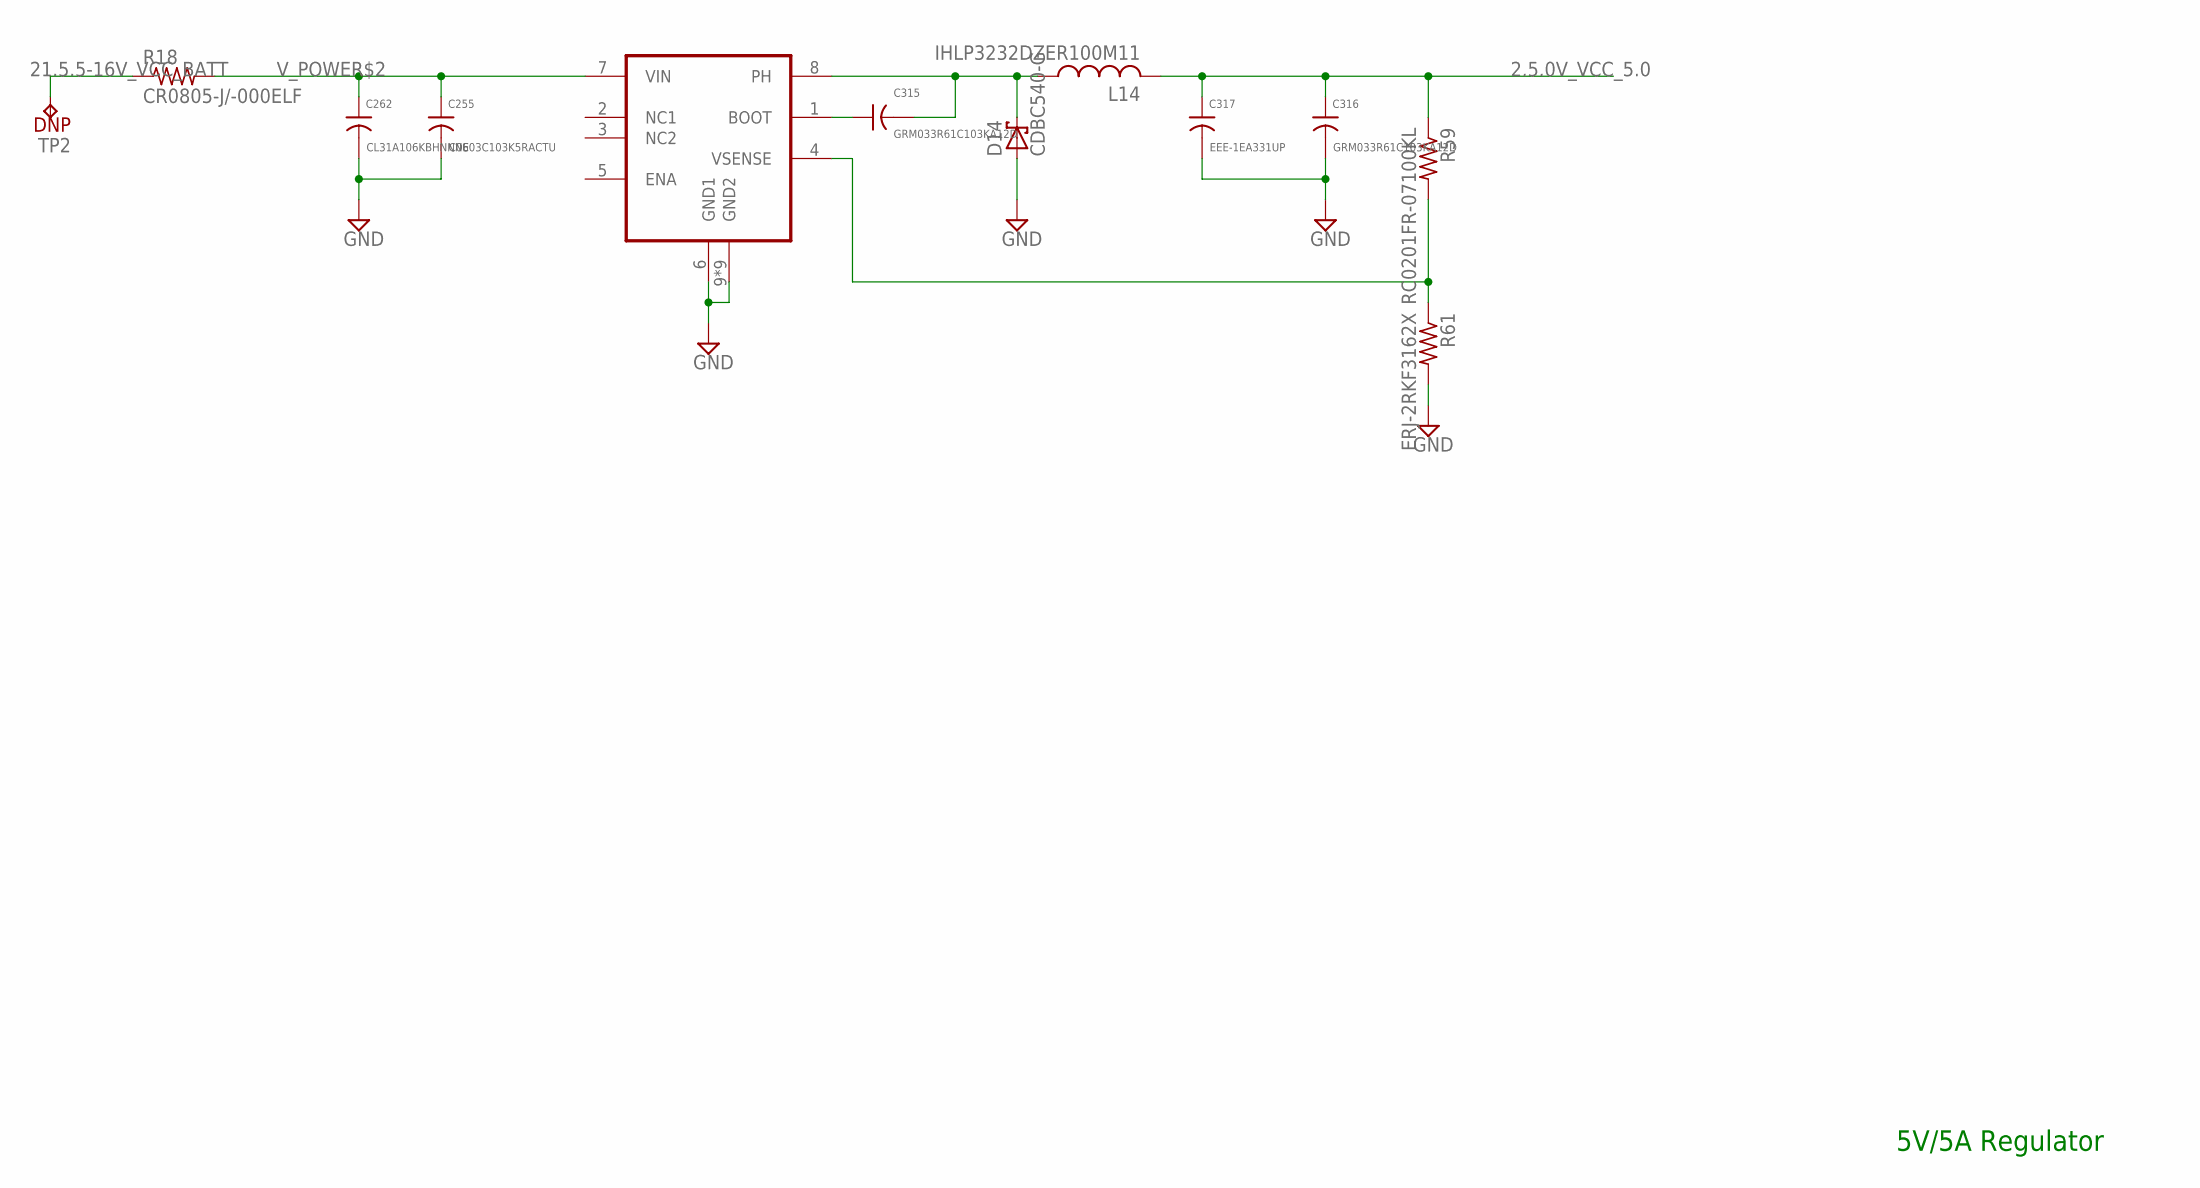
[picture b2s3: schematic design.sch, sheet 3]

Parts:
C255: C0603C103K5RACTU; 0603
C262: CL31A106KBHNNNE; 1206
C315, C316: GRM033R61C103KA12D; 0201
C317: EEE-1EA331UP; PANASONIC_F
D14: CDBC540-G; DO-214AB
L14: IHLP3232DZER100M11; 3232DZ
R18: CR0805-J/-000ELF; 0805
R59: RC0201FR-07100KL; 0201
R61: ERJ-2RKF3162X; 0402
TP2: DNP; TP0500
U17: TPS5450QDDARQ1; 8SO_POWERPAD

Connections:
2.5.0V_VCC_5.0: C316.1, C317.+ (1), L14.2, R59.1; also elsewhere on the board
21.5.5-16V_VCC_BATT: R18.1, TP2.1; also elsewhere on the board
BOOT$2: C315.1, U17.1 (BOOT)
GND: C255.2, C262.2, C316.2, C317.- (2), D14.A, R61.2, U17.6 (GND1), U17.9 (GND2), U17.PWRPAD1 (GND2), U17.PWRPAD2 (GND2), U17.PWRPAD3 (GND2), U17.PWRPAD4 (GND2), U17.PWRPAD5 (GND2), U17.PWRPAD6 (GND2), U17.PWRPAD7 (GND2), U17.PWRPAD8 (GND2); also elsewhere on the board
PH$2: C315.2, D14.C, L14.1, U17.8 (PH)
VSENSE$2: R59.2, R61.1, U17.4 (VSENSE)
V_POWER$2: C255.1, C262.1, R18.2, U17.7 (VIN)

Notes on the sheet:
5V/5A Regulator

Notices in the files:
parts and their libraries:
Wurth_Capacitors_WCAP-ATUL: Copyright: Würth Elektronik
SparkFun-Connectors: Licensing: Creative Commons ShareAlike 4.0 International - https://creativecommons.org/licenses/by-sa/4.0
COPYRIGHT: Copyright (C) 2018 Accelerated Designs. All rights reserved
